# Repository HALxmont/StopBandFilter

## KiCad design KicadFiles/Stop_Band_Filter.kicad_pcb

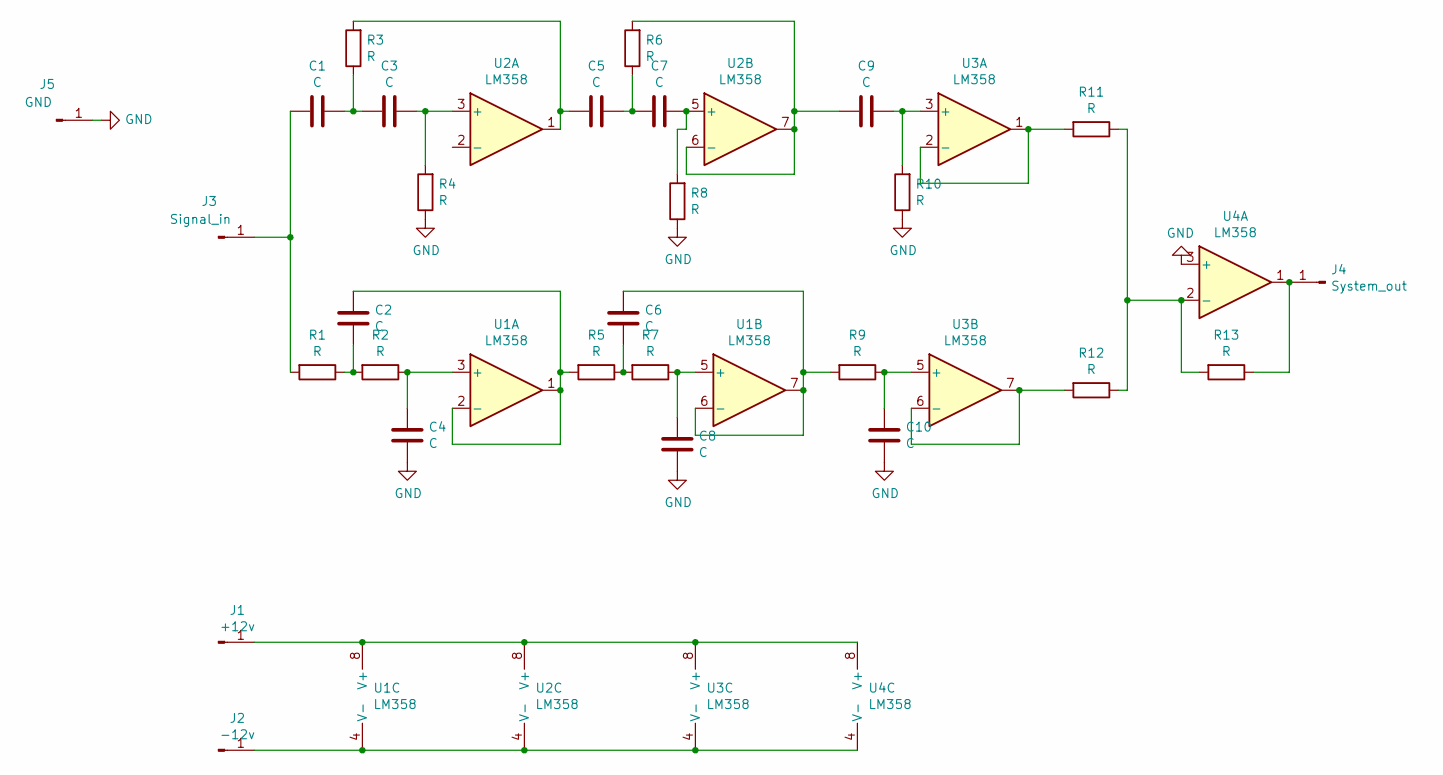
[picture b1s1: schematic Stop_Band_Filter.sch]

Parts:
C1, C2, C3, C4, C5, C6, C7, C8, C9, C10: C; C_0603_1608Metric_Pad1.05x0.95mm_HandSolder
J1: +12v; PinHeader_1x01_P1.00mm_Vertical
J2: -12v; PinHeader_1x01_P1.00mm_Vertical
J3: Signal_in; PinHeader_1x01_P1.00mm_Vertical
J4: System_out; PinHeader_1x01_P1.00mm_Vertical
J5: GND; PinHeader_1x01_P1.00mm_Vertical
R1, R2, R3, R4, R5, R6, R7, R8, R9, R10, R11, R12, R13: R; R_0603_1608Metric_Pad1.05x0.95mm_HandSolder
U1, U2, U3, U4: LM358; DIP-8_W7.62mm_Socket

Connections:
GND: C4.2, C8.2, C10.2, J5.1, R4.1, R8.1, R10.1, U4.3 (+); also elsewhere on the board
unnamed: C1.1, C3.2, R3.1
unnamed: C1.2, J3.1, R1.2
unnamed: C2.1, R5.2, U1.1, U1.2 (-)
unnamed: C2.2, R1.1, R2.2
unnamed: C3.1, R4.2, U2.3 (+)
unnamed: C4.1, R2.1, U1.3 (+)
unnamed: C5.1, C7.2, R6.1
unnamed: C5.2, R3.2, U2.1
unnamed: C6.1, R9.2, U1.6 (-), U1.7
unnamed: C6.2, R5.1, R7.2
unnamed: C7.1, R8.2, U2.5 (+)
unnamed: C8.1, R7.1, U1.5 (+)
unnamed: C9.1, R10.2, U3.3 (+)
unnamed: C9.2, R6.2, U2.6 (-), U2.7
unnamed: C10.1, R9.1, U3.5 (+)
unnamed: J1.1, U1.8 (V+), U2.8 (V+), U3.8 (V+), U4.8 (V+)
unnamed: J2.1, U1.4 (V-), U2.4 (V-), U3.4 (V-), U4.4 (V-)
unnamed: J4.1, R13.1, U4.1
unnamed: R11.1, R12.1, R13.2, U4.2 (-)
unnamed: R11.2, U3.1, U3.2 (-)
unnamed: R12.2, U3.6 (-), U3.7

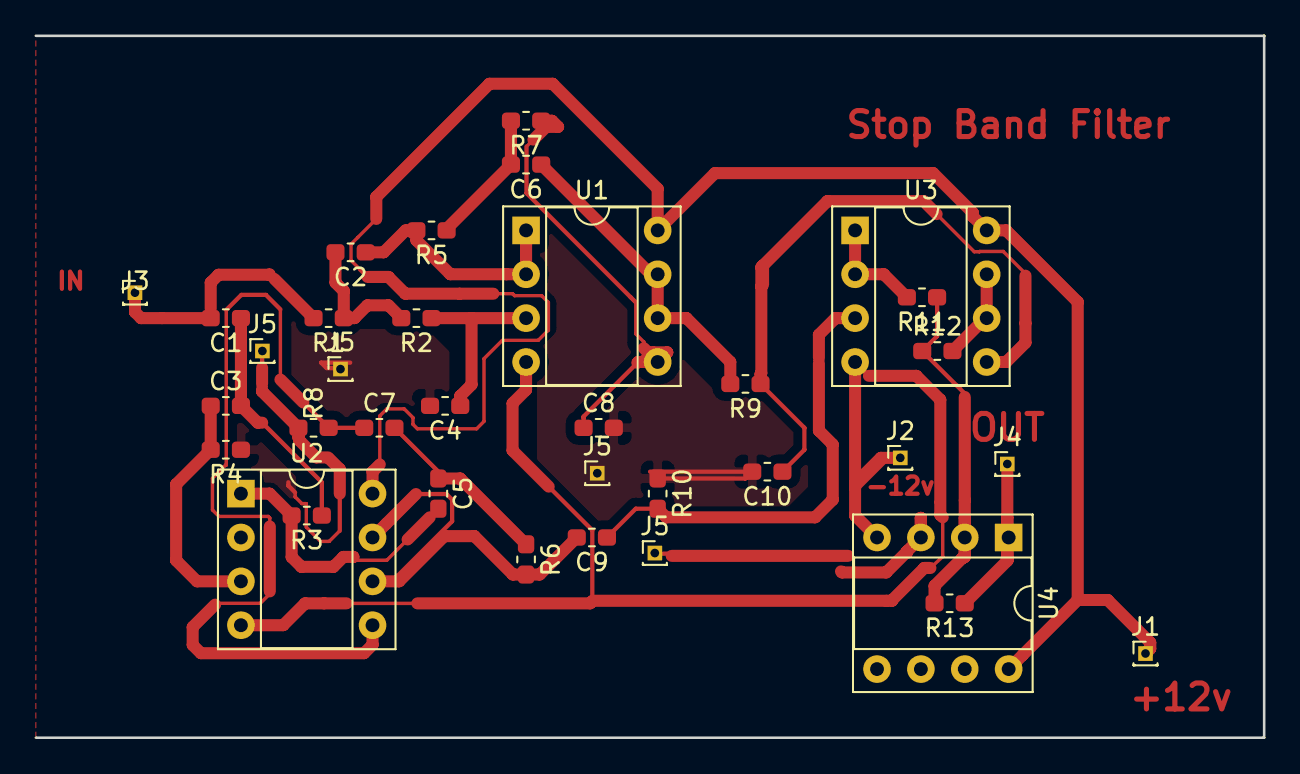
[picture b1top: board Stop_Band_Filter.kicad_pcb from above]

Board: 2 copper layers, 71.1 x 40.6 mm, 35 parts (0 on the bottom side), 22 nets.

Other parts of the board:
J5#2, J5#3, J5#4: GND; PinHeader_1x01_P1.00mm_Vertical

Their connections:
GND: J5#4.1; also elsewhere on the board

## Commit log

2019-01-20 First files upload
2019-01-20 Spice simulation update
2019-01-20 General Update
2019-02-21 update files
2019-03-13 inform upload
